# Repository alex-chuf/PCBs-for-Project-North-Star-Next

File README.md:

This USB3 Hub board is specially used on some AR/VR DIY project, that requires: 

-less cable connect to the host machine
-need to connect at least 2 USB camera sensors, or other sensors that work on USB2 or USB3
-keep the USB3 hub size as small as possible 

Why do you need it? 

I recently worked on an AR project called project north star. I found there was an issue with connecting the sensors to the host , normally we will use at least 2 camera sensor (e.g. Ultraleap IR170, Intelrealsense T261/T265), these sensors can both work on USB2 and USB3. You may connect them to a cheap and small size USB2 hub, but the problem is, there is no enough bandwidth to support two sensors on a same USB2 hub. You will face laggy and latency issues. 

So I made this USB3 hub, with features: 
-Small size, so you can easily put into your headset
-4x USB 3 downstream ports, support both USB2 and USB3
-up to 5Gbit/s USB3 bandwidth, more than enough to support even three USB3 sensors at the same time
-USB3 type C cable input
-A cooling fan connector
-An exposed soldering pad for 5V and GND, so you can possibly power other devices from it.
Note: normally the host machine can output 5V/1A power on the USB3 port. 

Specifications: 
-Dimension: 37.8*23.0mm
-Weight: 4.8g
-PCB thickness: 1.6mm
-USB3 hub chip: GL3523
-Bandwidth: 5Gbit/s
-Total Max. power on all ports: 5V1A

Available USB3 adapter for sensors:
-IR170
-T261/265
-XR50/USB2

Planning: 
-LM2 

contact me if there is one not on the list

Packing List:

1x USB3 hub board v1.05
4x 12P ribbon cable 10cm

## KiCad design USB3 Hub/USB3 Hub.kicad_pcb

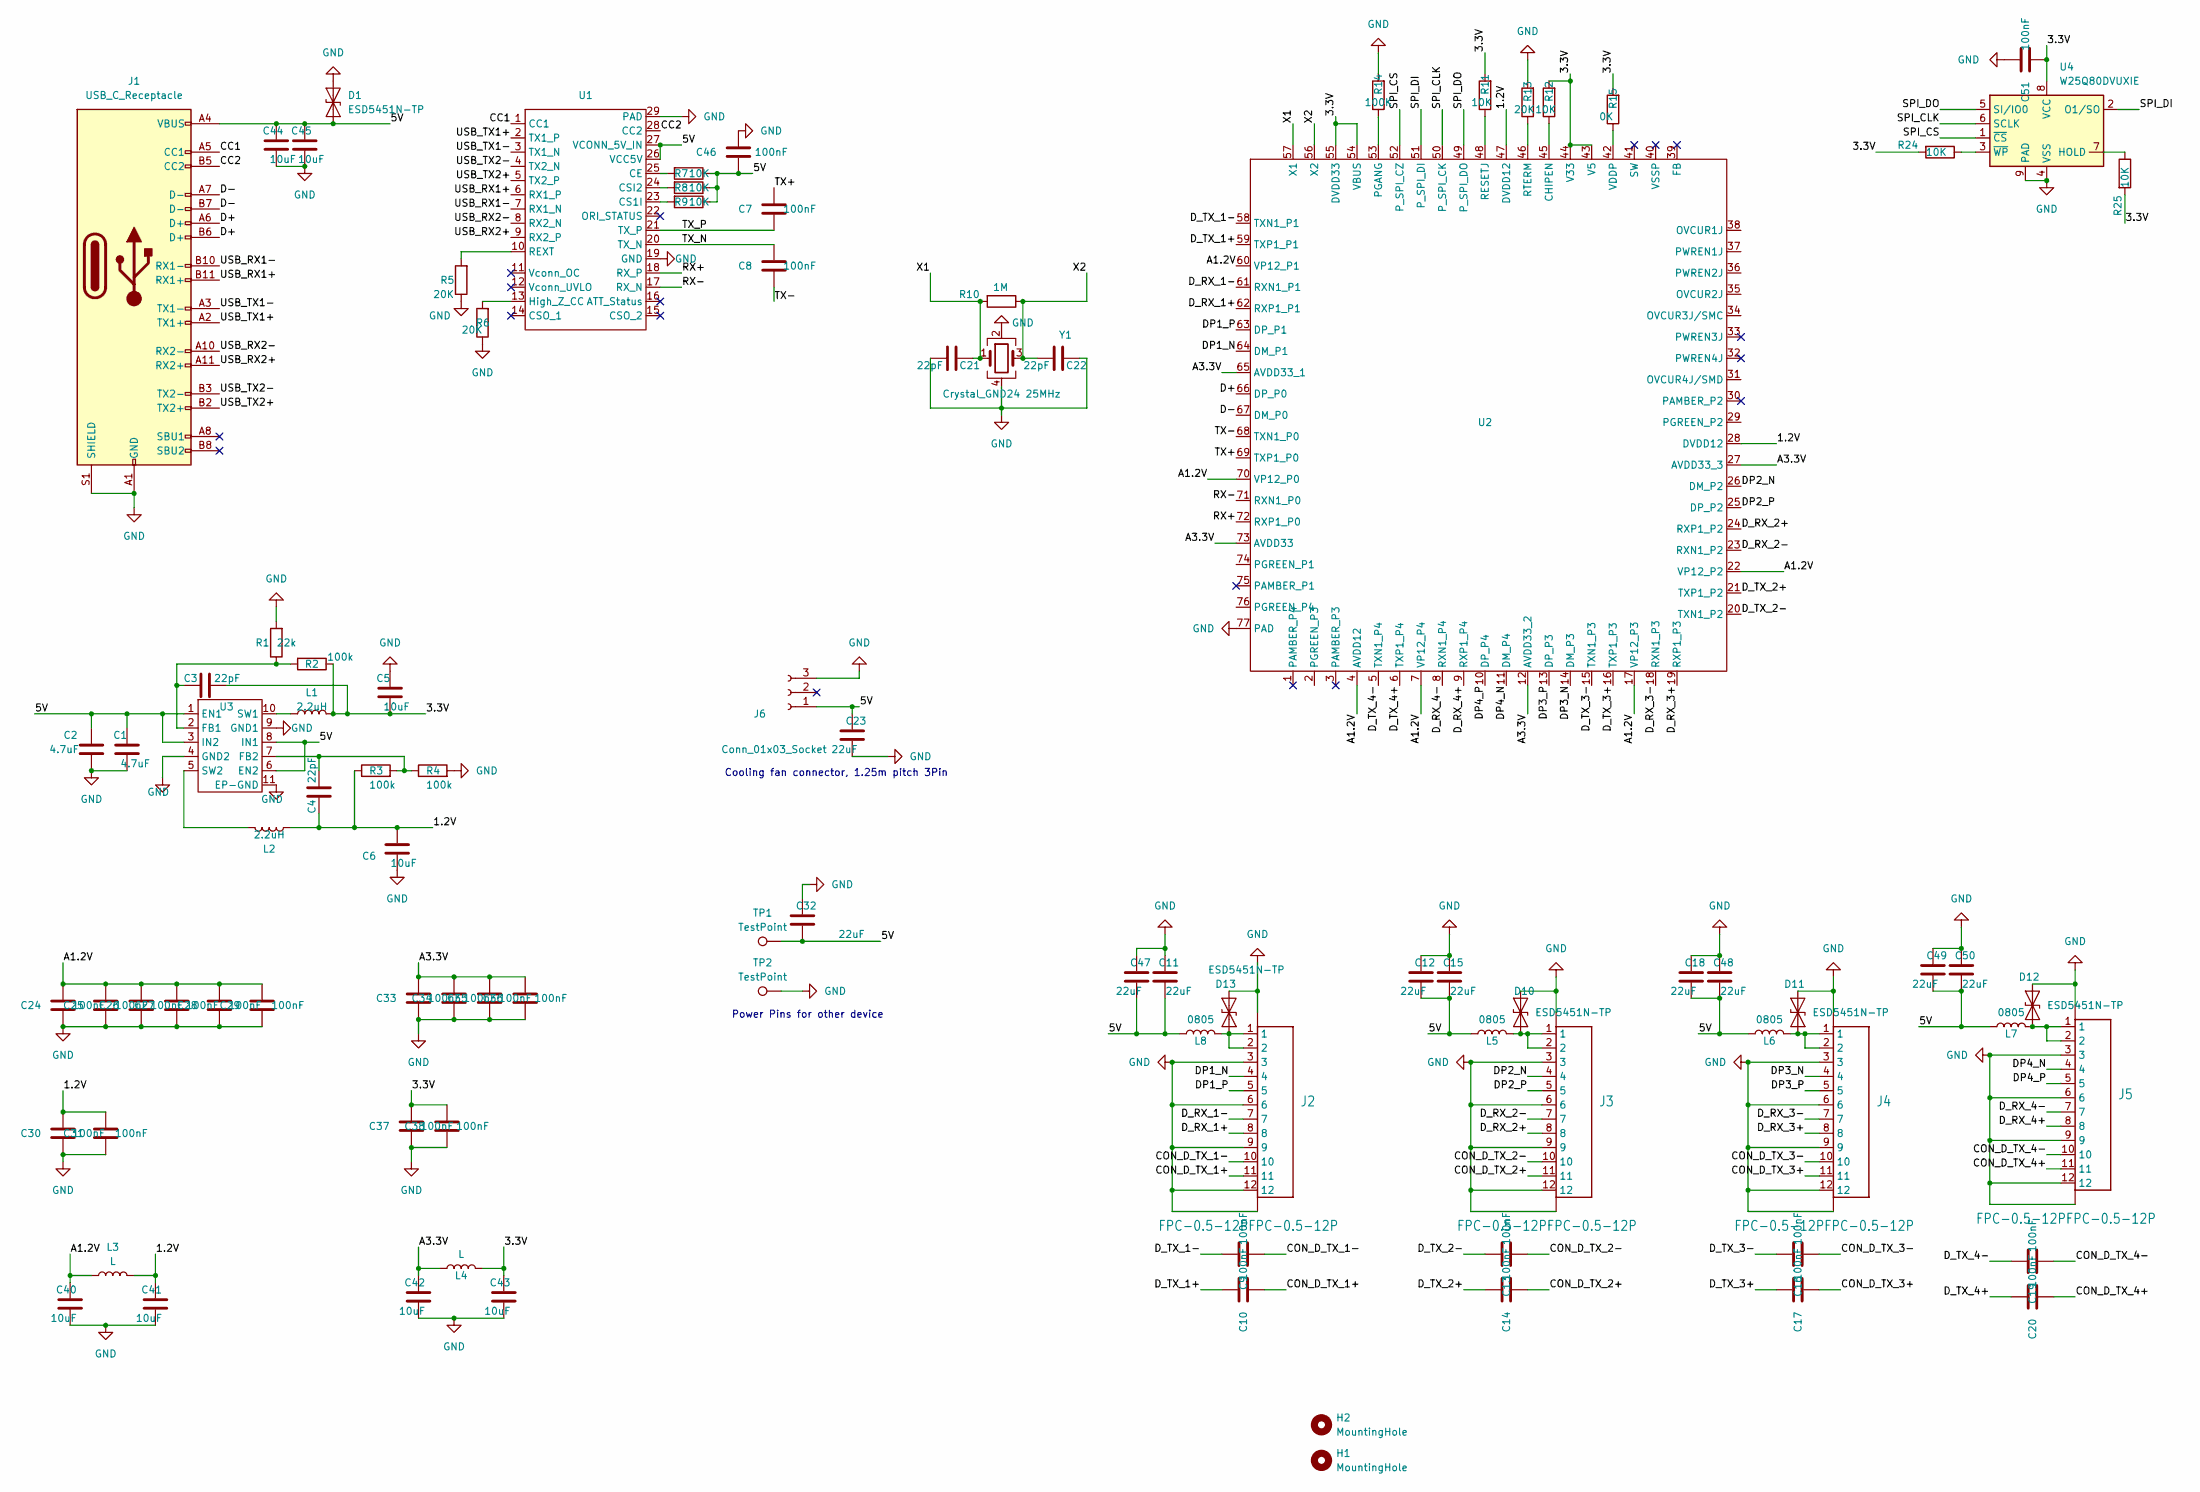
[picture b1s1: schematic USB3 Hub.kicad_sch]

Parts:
C1, C2: 4.7uF; C_0603_1608Metric
C3, C4, C21, C22: 22pF; C_0201_0603Metric
C5, C6, C40, C41, C42, C43, C44, C45: 10uF; C_0603_1608Metric
C7, C8, C9, C10, C13, C14, C16, C17, C19, C20, C24, C25, C26, C27, C28, C29, C30, C31, C33, C34, C35, C36, C37, C38, C46, C51: 100nF; C_0201_0603Metric
C11, C12, C15, C18, C23, C32, C47, C48, C49, C50: 22uF; C_0603_1608Metric
D1, D10, D11, D12, D13: ESD5451N-TP; D_0402_1005Metric
H1, H2: MountingHole; MountingHole_2.2mm_M2_DIN965_Pad
J1: USB_C_Receptacle; USB_C_Receptacle_Amphenol_12401548E4-2A
J2, J3, J4, J5: FPC-0.5-12PFPC-0.5-12P; FPC-0.5-12P
J6: Conn_01x03_Socket; SH1.25mm_3P_horizon
L1, L2: 2.2uH; 2016(L1.0)
L3, L4: L; L_0402_1005Metric
L5, L6, L7, L8: 0805; L_0805_2012Metric
R1: 22k; R_0201_0603Metric
R2, R3, R4: 100k; R_0201_0603Metric
R5, R6, R13: 20K; R_0201_0603Metric
R7, R8, R9, R11, R12, R24, R25: 10K; R_0201_0603Metric
R10: 1M; R_0201_0603Metric
R14: 100K; R_0201_0603Metric
R15: 0K; R_0201_0603Metric
TP1, TP2: TestPoint; TestPoint_Pad_1.5x1.5mm
U1: VL160
U2: GL3523-QFN76
U3: RY1302
U4: W25Q80DVUXIE; USON8_2X3MM
Y1: Crystal_GND24 25MHz; Crystal_SMD_3225-4Pin_3.2x2.5mm

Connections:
/1.2V: C4.2, C6.2, C30.1, C31.1, C41.1, L2.1, L3.2, R3.1, U2.28 (DVDD12), U2.47 (DVDD12)
/3.3V: C3.1, C5.1, C37.1, C38.1, C43.1, C51.2, L1.2, L4.2, R2.1, R11.2, R12.2, R15.2, R24.2, R25.2, U2.43 (V5), U2.44 (V33), U2.54 (VBUS), U2.55 (DVDD33), U4.8 (VCC)
/5V: C1.2, C2.2, C11.1, C12.1, C15.1, C18.1, C23.2, C32.1, C44.2, C45.2, C46.2, C47.1, C48.1, C49.1, C50.1, D1.1 (A1), J1.A4 (VBUS), J1.A9 (VBUS), J1.B4 (VBUS), J1.B9 (VBUS), J6.1, L5.1, L6.1, L7.1, L8.1, R7.1, R8.1, R9.1, TP1.1, U1.26 (VCC5V), U1.27 (VCONN_5V_IN), U3.1 (EN1), U3.3 (IN2), U3.6 (EN2), U3.8 (IN1)
/A1.2V: C24.1, C25.1, C26.1, C27.1, C28.1, C29.1, C40.1, L3.1, U2.4 (AVDD12), U2.7 (VP12_P4), U2.17 (VP12_P3), U2.22 (VP12_P2), U2.60 (VP12_P1), U2.70 (VP12_P0)
/A3.3V: C33.1, C34.1, C35.1, C36.1, C42.1, L4.1, U2.12 (AVDD33_2), U2.27 (AVDD33_3), U2.65 (AVDD33_1), U2.73 (AVDD33)
/CC1: J1.A5 (CC1), U1.1 (CC1)
/CC2: J1.B5 (CC2), U1.28 (CC2)
/CON_D_TX_1+: C10.2, J2.11
/CON_D_TX_1-: C9.2, J2.10
/CON_D_TX_2+: C14.2, J3.11
/CON_D_TX_2-: C13.2, J3.10
/CON_D_TX_3+: C17.2, J4.11
/CON_D_TX_3-: C16.2, J4.10
/CON_D_TX_4+: C20.2, J5.11
/CON_D_TX_4-: C19.2, J5.10
/D+: J1.A6 (D+), J1.B6 (D+), U2.66 (DP_P0)
/D-: J1.A7 (D-), J1.B7 (D-), U2.67 (DM_P0)
/DP1_N: J2.4, U2.64 (DM_P1)
/DP1_P: J2.5, U2.63 (DP_P1)
/DP2_N: J3.4, U2.26 (DM_P2)
/DP2_P: J3.5, U2.25 (DP_P2)
/DP3_N: J4.4, U2.14 (DM_P3)
/DP3_P: J4.5, U2.13 (DP_P3)
/DP4_N: J5.4, U2.11 (DM_P4)
/DP4_P: J5.5, U2.10 (DP_P4)
/D_RX_1+: J2.8, U2.62 (RXP1_P1)
/D_RX_1-: J2.7, U2.61 (RXN1_P1)
/D_RX_2+: J3.8, U2.24 (RXP1_P2)
/D_RX_2-: J3.7, U2.23 (RXN1_P2)
/D_RX_3+: J4.8, U2.19 (RXP1_P3)
/D_RX_3-: J4.7, U2.18 (RXN1_P3)
/D_RX_4+: J5.8, U2.9 (RXP1_P4)
/D_RX_4-: J5.7, U2.8 (RXN1_P4)
/D_TX_1+: C10.1, U2.59 (TXP1_P1)
/D_TX_1-: C9.1, U2.58 (TXN1_P1)
/D_TX_2+: C14.1, U2.21 (TXP1_P2)
/D_TX_2-: C13.1, U2.20 (TXN1_P2)
/D_TX_3+: C17.1, U2.16 (TXP1_P3)
/D_TX_3-: C16.1, U2.15 (TXN1_P3)
/D_TX_4+: C20.1, U2.6 (TXP1_P4)
/D_TX_4-: C19.1, U2.5 (TXN1_P4)
/RX+: U1.18 (RX_P), U2.72 (RXP1_P0)
/RX-: U1.17 (RX_N), U2.71 (RXN1_P0)
/SPI_CLK: U2.50 (P_SPI_CK), U4.6 (SCLK)
/SPI_CS: U2.52 (P_SPI_CZ), U4.1 (~CS)
/SPI_DI: U2.51 (P_SPI_DI), U4.2 (O1/SO)
/SPI_DO: U2.49 (P_SPI_DO), U4.5 (SI/IO0)
/TX+: C7.1, U2.69 (TXP1_P0)
/TX-: C8.2, U2.68 (TXN1_P0)
/TX_N: C8.1, U1.20 (TX_N)
/TX_P: C7.2, U1.21 (TX_P)
/USB_RX1+: J1.B11 (RX1+), U1.6 (RX1_P)
/USB_RX1-: J1.B10 (RX1-), U1.7 (RX1_N)
/USB_RX2+: J1.A11 (RX2+), U1.9 (RX2_P)
/USB_RX2-: J1.A10 (RX2-), U1.8 (RX2_N)
/USB_TX1+: J1.A2 (TX1+), U1.2 (TX1_P)
/USB_TX1-: J1.A3 (TX1-), U1.3 (TX1_N)
/USB_TX2+: J1.B2 (TX2+), U1.5 (TX2_P)
/USB_TX2-: J1.B3 (TX2-), U1.4 (TX2_N)
/X1: C21.2, R10.2, U2.57 (X1), Y1.1
/X2: C22.1, R10.1, U2.56 (X2), Y1.3
GND: C1.1, C2.1, C5.2, C6.1, C11.2, C12.2, C15.2, C18.2, C21.1, C22.2, C23.1, C24.2, C25.2, C26.2, C27.2, C28.2, C29.2, C30.2, C31.2, C32.2, C33.2, C34.2, C35.2, C36.2, C37.2, C38.2, C40.2, C41.2, C42.2, C43.2, C44.1, C45.1, C46.1, C47.2, C48.2, C49.2, C50.2, C51.1, D1.2 (A2), D10.2 (A2), D11.2 (A2), D12.2 (A2), D13.2 (A2), J1.A1 (GND), J1.A12 (GND), J1.B1 (GND), J1.B12 (GND), J1.S1 (SHIELD), J2.3, J2.6, J2.9, J2.12, J2.P$13 (G1), J2.P$14 (G2), J3.3, J3.6, J3.9, J3.12, J3.P$13 (G1), J3.P$14 (G2), J4.3, J4.6, J4.9, J4.12, J4.P$13 (G1), J4.P$14 (G2), J5.3, J5.6, J5.9, J5.12, J5.P$13 (G1), J5.P$14 (G2), J6.3, R1.2, R4.2, R5.1, R6.1, R13.2, R14.2, TP2.1, U1.19 (GND), U1.29 (PAD), U2.77 (PAD), U3.4 (GND2), U3.9 (GND1), U3.11 (EP-GND), U4.4 (VSS), U4.9 (PAD), Y1.2, Y1.4
unnamed: D10.1 (A1), J3.1, J3.2, L5.2
unnamed: D11.1 (A1), J4.1, J4.2, L6.2
unnamed: D12.1 (A1), J5.1, J5.2, L7.2
unnamed: D13.1 (A1), J2.1, J2.2, L8.2
unnamed: R7.2, U1.25 (CE)
unnamed: R9.2, U1.23 (CS1I)
unnamed: R8.2, U1.24 (CSI2)
unnamed: R6.2, U1.13 (High_Z_CC)
unnamed: R5.2, U1.10 (REXT)
unnamed: R12.1, U2.45 (CHIPEN)
unnamed: R14.1, U2.53 (PGANG)
unnamed: R11.1, U2.48 (RESETJ)
unnamed: R13.1, U2.46 (RTERM)
unnamed: R15.1, U2.42 (VDDP)
unnamed: C3.2, R1.1, R2.2, U3.2 (FB1)
unnamed: C4.1, R3.2, R4.1, U3.7 (FB2)
unnamed: L1.1, U3.10 (SW1)
unnamed: L2.2, U3.5 (SW2)
unnamed: R25.1, U4.7 (HOLD)
unnamed: R24.1, U4.3 (~WP)

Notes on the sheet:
Power Pins for other device
Cooling fan connector, 1.25m pitch 3Pin

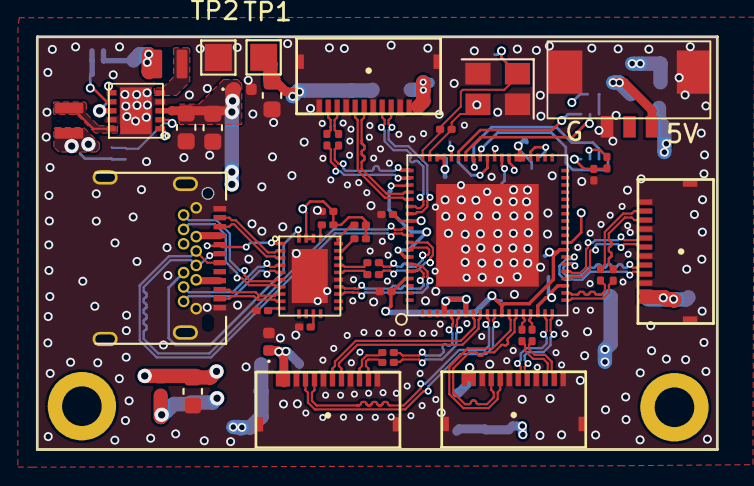
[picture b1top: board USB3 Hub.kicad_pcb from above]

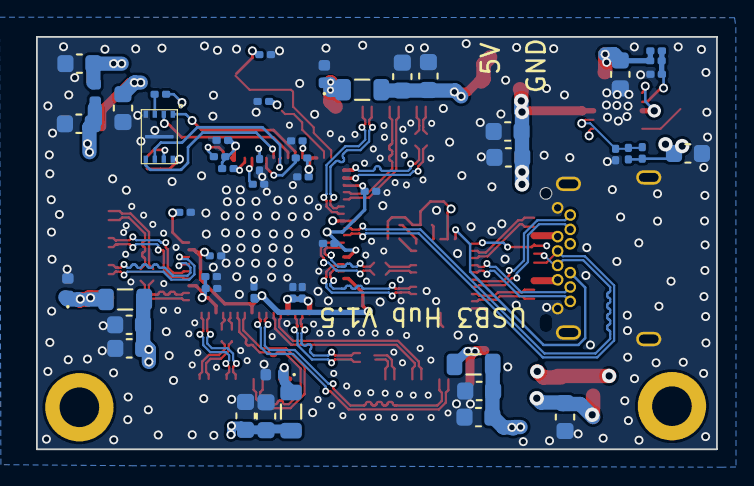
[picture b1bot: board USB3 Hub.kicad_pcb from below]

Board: 4 copper layers, 37.8 x 22.9 mm, 95 parts (51 on the bottom side), 82 nets.

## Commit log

2024-07-31 Create USB3 Hub GL3523
